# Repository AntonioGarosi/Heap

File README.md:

# Heap
### by Antonio Garosi

Heap is a kid-targeted interactive game aimed at promoting cooperation, fast-thinking and consequentiality.
Ideally, it's a [Tangram](https://en.wikipedia.org/wiki/Tangram) meets [Jenga](https://en.wikipedia.org/wiki/Jenga) meets [Operation](https://en.wikipedia.org/wiki/Operation_(game)) game (this salad is also heavily seasoned with [Beasts of Balance](https://beastsofbalance.com/)'s sauce).

The game was initially conceived to be themed about ecological issues, and the questions are accordingly based on reports about italian waste production.
Expanding the game to other subjects is just a matter of choosing new pairings of questions and answers, coding them and updating the game firmware.

As of October 2018, the most tested version of the game is based of the following rules:

* The players have at their disposal a pool of blocks and tiles.
* Blocks of different materials represents different waste byproducts: natural wood for paper, blue acrylic for plastics, white and red PLA for generic waste. Each block also represents a quantity expressed by its size. Each cube it is made of represents 10kg.
* Each tile is numbered and represents a question.
* The players start a question by placing a card over the central base of the game. Each question is about quantity and they can replied by placing the blocks over the tile.
* If the amount and type of blocks placed over the tile properly answers its question the players can keep building the heap by adding tiles and blocks and so on.
* If the players the players place the wrong amount or type of blocks, the base shakes and the heap crumbles.
* If the players don't reply quick enough, the base shakes and the heap crumbles.
* If the players inadvertently remove or make fall blocks from the heap, the base shakes and ...yep, the heap crumbles.
* If the heap crumbles down, the game is lost.

Full explanation and production details of the project can be found in the [original documentation](http://fab.academany.org/2018/labs/fablabsiena/students/antonio-garosi/final-project/), realized as a final project for my Fab Academy course in 2018.

Everything regarding Heap is under [Creative Commons BY-SA 4.0](https://creativecommons.org/licenses/by-sa/4.0/). Respect this will and everything will be just fine.

For any reason, just [contact me](mailto:antonio_garosi@yahoo.it)

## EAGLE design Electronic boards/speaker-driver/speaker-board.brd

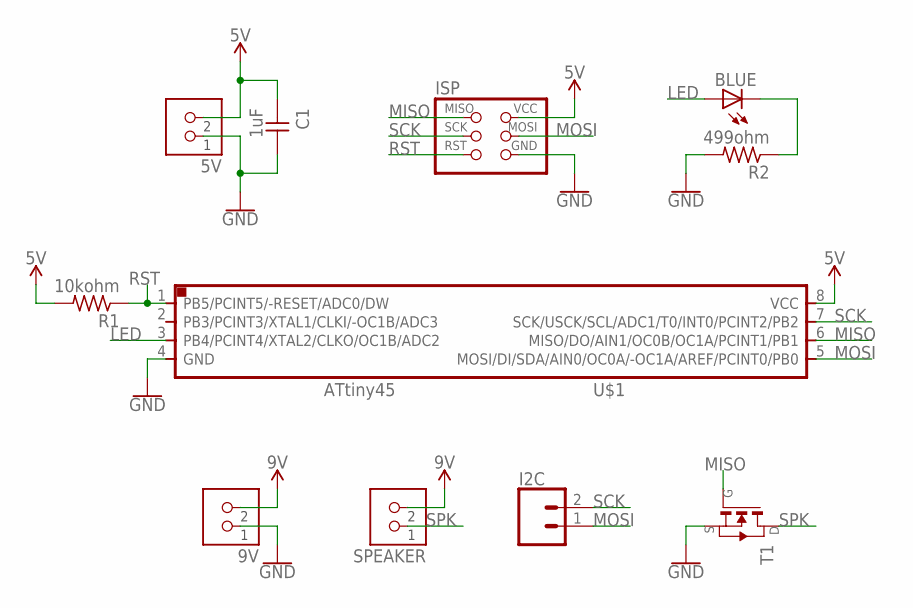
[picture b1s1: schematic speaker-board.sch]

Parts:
5V, 9V: TERM-1X02-FABLAB; ED555DS-2DS
BLUE: LEDFAB1206; LED1206FAB
C1: 1uF; C1206FAB
I2C: CONN_021X02_NO_SILK; 1X02_NO_SILK
ISP: AVRISPSMD; 2X03SMD
R1: 10kohm; R1206FAB
R2: 499ohm; R1206FAB
SPEAKER: TERM-1X02-FABLAB; ED555DS-2DS
T1: NMOSFETSOT23; SOT-23
U$1: ATTINY45SI; SOIC8

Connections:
GND: 5V.1, 9V.1, C1.2, ISP.6 (GND), R2.2, T1.2 (S), U$1.4 (GND)
LED: BLUE.1 (A), U$1.3 (PB4/PCINT4/XTAL2/CLKO/OC1B/ADC2)
MISO: ISP.1 (MISO), T1.3 (G), U$1.6 (MISO/DO/AIN1/OC0B/OC1A/PCINT1/PB1)
MOSI: I2C.1, ISP.4 (MOSI), U$1.5 (MOSI/DI/SDA/AIN0/OC0A/-OC1A/AREF/PCINT0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)
unnamed: BLUE.2 (C), R2.1
RST: ISP.5 (RST), R1.1, U$1.1 (PB5/PCINT5/-RESET/ADC0/DW)
SCK: I2C.2, ISP.3 (SCK), U$1.7 (SCK/USCK/SCL/ADC1/T0/INT0/PCINT2/PB2)
SPK: SPEAKER.1, T1.1 (D)
VCC_1: 5V.2, C1.1, ISP.2 (VCC), R1.2, U$1.8 (VCC)
VCC_2: 9V.2, SPEAKER.2

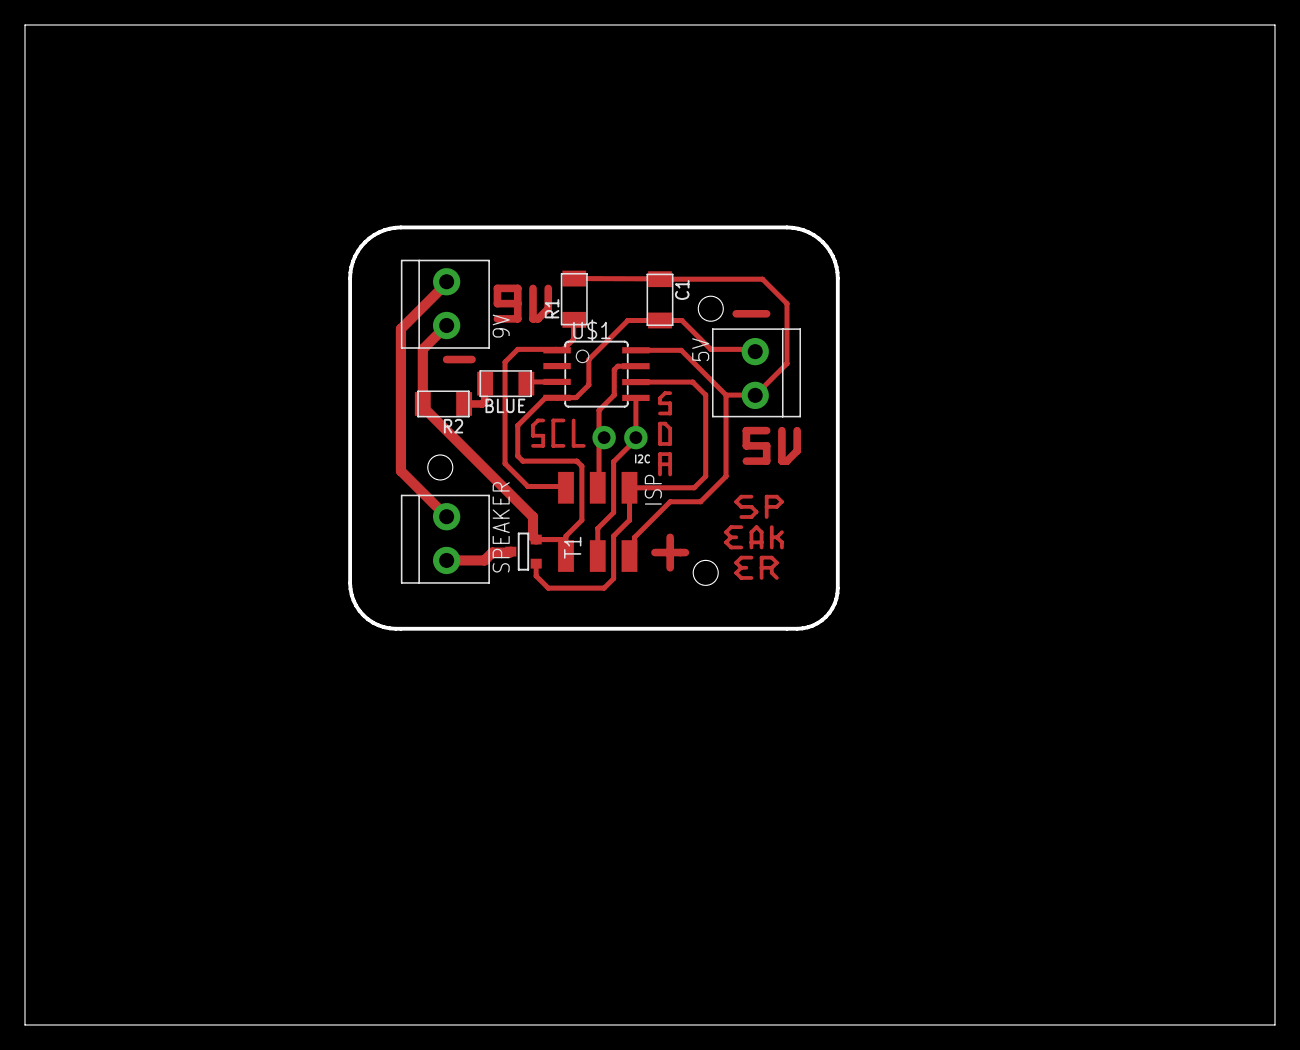
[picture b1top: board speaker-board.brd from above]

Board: 2 copper layers, 100.0 x 80.0 mm, 11 parts (0 on the bottom side), 10 nets.

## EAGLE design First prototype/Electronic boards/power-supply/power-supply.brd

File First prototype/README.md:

# Heap
### by Antonio Garosi - July 2018

**This files hold the design of the very first, complete, functional prototype made as final project for my Fab Academy 2018 course.
The root of this repository will be continuosly updated but this folder will always remain as is to remark the starting point of this project.**

Heap is a kid-targeted interactive game about waste production, aimed at promoting cooperation, fast-thinking and consequentiality.
Ideally, it's a game where [Tangram](https://en.wikipedia.org/wiki/Tangram) meets [Jenga](https://en.wikipedia.org/wiki/Jenga) meets [Operation](https://en.wikipedia.org/wiki/Operation_(game)).
The rules are by design loose and open, but essentially they are as such:

* The players are presented with a pool filled with a set of cards representing daily items and various blocks of different colors and shapes;

* Within a time span, the players have to choose among one of the cards and put it on the base at the center of the pool;

* Then, within another and shorter time span, the players will have to put over the card a precise amount of blocks, trying to recreate the figure over the card. The material of the block represents a different kind of waste, so, in addition to the shape, the players will have to guess the material of which the item over the card is made of;

* A load sensor under the base evaluates the blocks over the card. The more the load is far from the corresponding value, the more more the base will begin to nervously buzz and shake;

* If the stack is still in place new cards and blocks can be added. If the stack tumbles down the game will start all over again;

Full explanation and production details of the project can be found in the [original documentation](http://fab.academany.org/2018/labs/fablabsiena/students/antonio-garosi/final-project/), realized as a final project for my Fab Academy course in 2018.

Everything regarding Heap is under [Creative Commons BY-SA 4.0](https://creativecommons.org/licenses/by-sa/4.0/). Respect this will and everything will be just fine.

For any reason, just [contact me](mailto:antonio_garosi@yahoo.it).

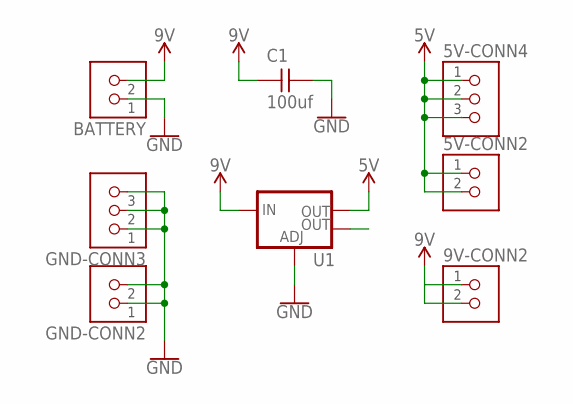
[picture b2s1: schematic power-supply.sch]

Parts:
5V-CONN2, 9V-CONN2: TERM-1X02-FABLAB; ED555DS-2DS
5V-CONN4: TERM-1X03'-FABLAB'; ED555DS-3DS
BATTERY: TERM-1X02-FABLAB; ED555DS-2DS
C1: 100uf; C1206FAB
GND-CONN2: TERM-1X02-FABLAB; ED555DS-2DS
GND-CONN3: TERM-1X03'-FABLAB'; ED555DS-3DS
U1: V_REG_LM1117SOT223; SOT223

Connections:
5V: 5V-CONN2.1, 5V-CONN2.2, 5V-CONN4.1, 5V-CONN4.2, 5V-CONN4.3, U1.2 (OUT)
9V: 9V-CONN2.1, 9V-CONN2.2, BATTERY.2, C1.1, U1.3 (IN)
GND: BATTERY.1, C1.2, GND-CONN2.1, GND-CONN2.2, GND-CONN3.1, GND-CONN3.2, GND-CONN3.3, U1.1 (ADJ)

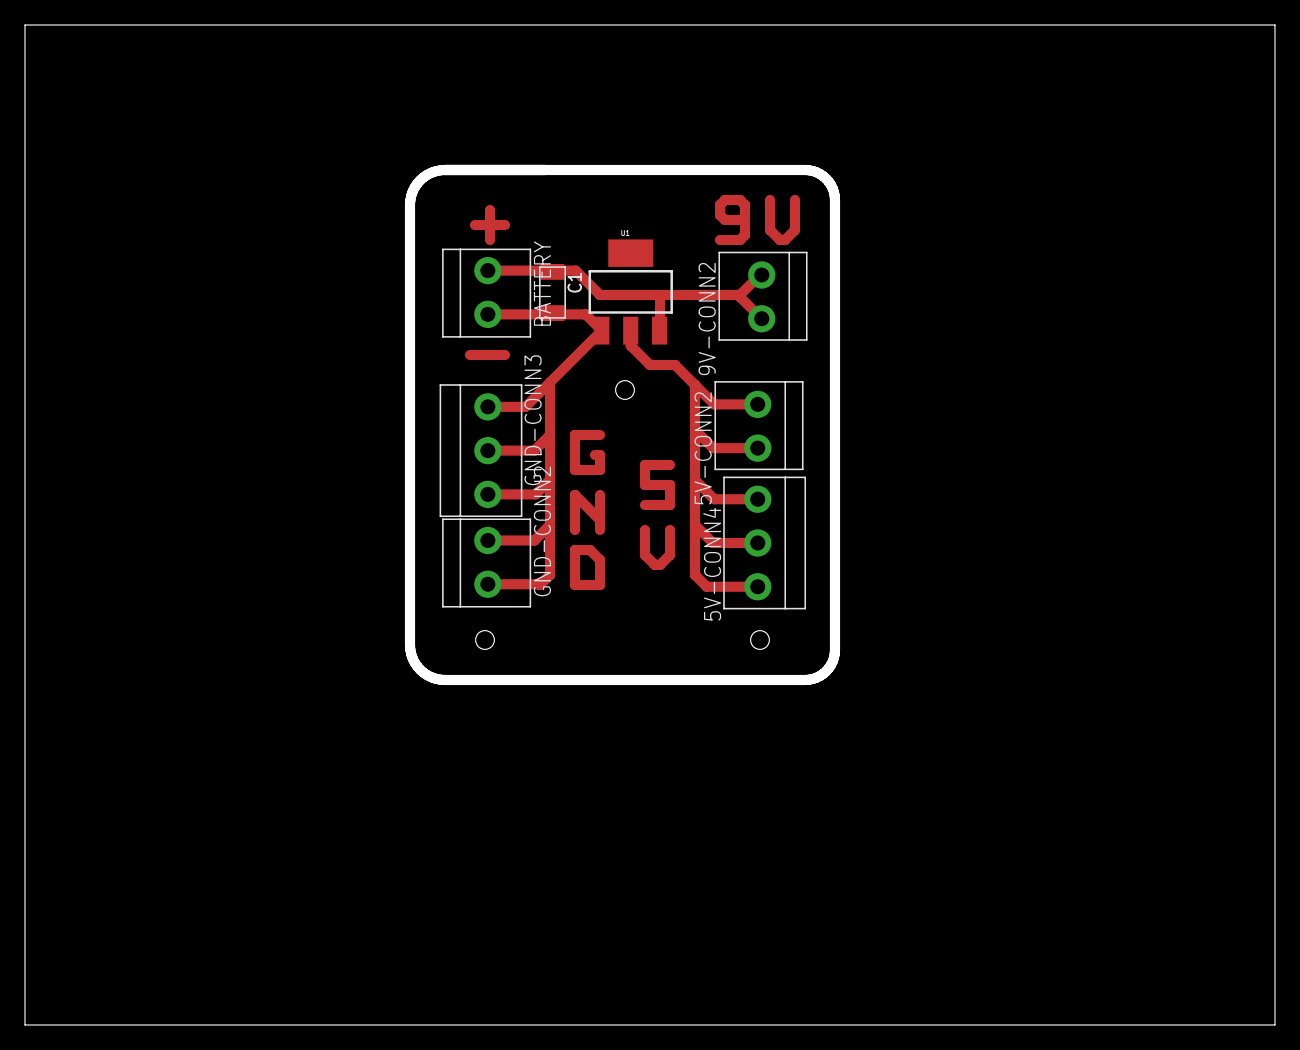
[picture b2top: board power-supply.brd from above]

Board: 2 copper layers, 100.0 x 80.0 mm, 8 parts (0 on the bottom side), 3 nets.

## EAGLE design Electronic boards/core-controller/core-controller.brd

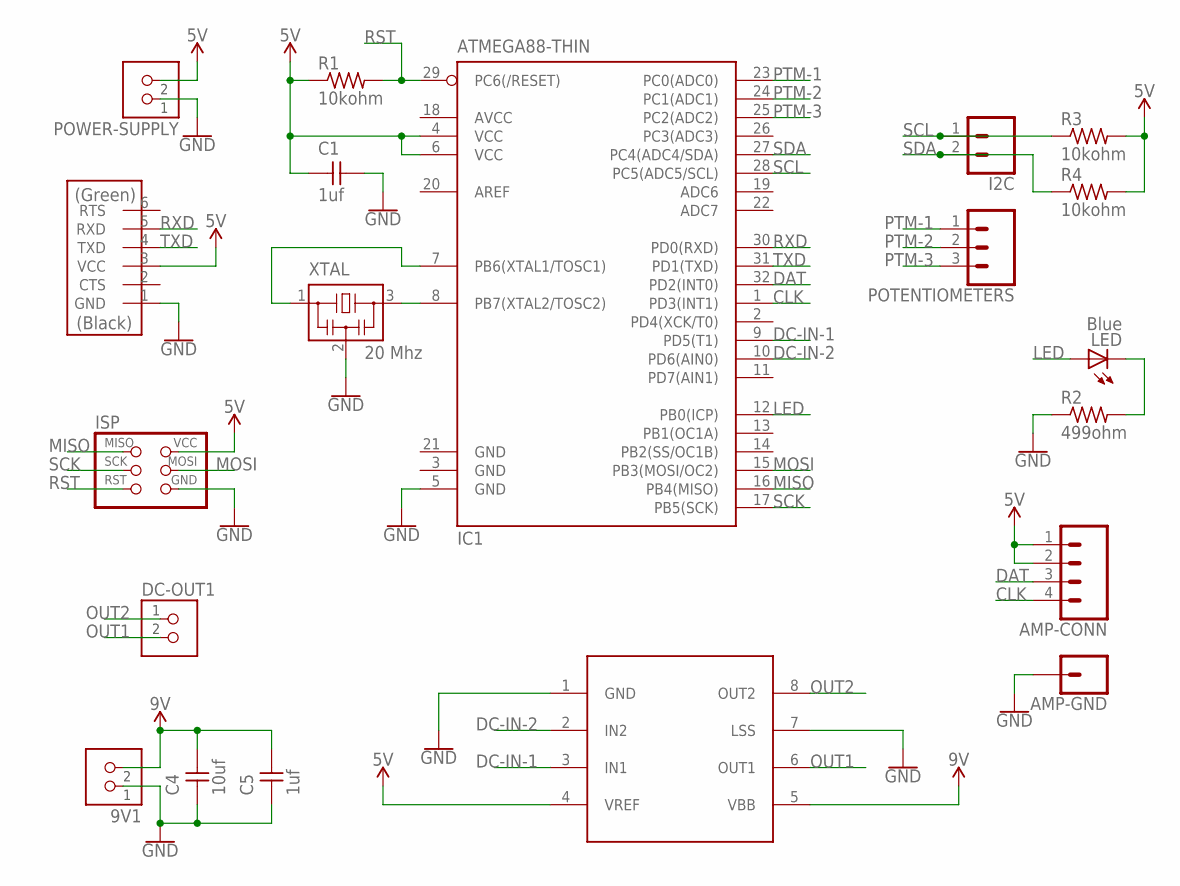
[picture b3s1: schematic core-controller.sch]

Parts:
9V1: TERM-1X02-FABLAB; ED555DS-2DS
AMP-CONN: CONN_041X04_NO_SILK; 1X04_NO_SILK
AMP-GND: CONN_01PTH_NO_SILK_YES_STOP; 1X01_NO_SILK
C1, C5: 1uf; C1206FAB
C4: 10uf; C1206FAB
DC-OUT1: TERM-1X02-FABLAB; ED555DS-2DS
FTDI: FTDI; 1X06SMD
I2C: CONN_021X02_NO_SILK; 1X02_NO_SILK
IC1: ATMEGA88-THIN; TQFP32-08THIN
ISP: AVRISPSMD; 2X03SMD
LED: Blue; LED1206FAB
POTENTIOMETERS: CONN_031X03_NO_SILK; 1X03_NO_SILK
POWER-SUPPLY: TERM-1X02-FABLAB; ED555DS-2DS
R1, R3, R4: 10kohm; R1206FAB
R2: 499ohm; R1206FAB
U$2: A4953; SOIC8
XTAL: 20 Mhz; EFOBM

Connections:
5V: AMP-CONN.1, AMP-CONN.2, C1.1, FTDI.3 (VCC), IC1.4 (VCC), IC1.6 (VCC), ISP.2 (VCC), POWER-SUPPLY.2, R1.1, R3.2, R4.2, U$2.4 (VREF)
AVCC: IC1.18 (AVCC)
CLK: AMP-CONN.4, IC1.1 (PD3(INT1))
DAT: AMP-CONN.3, IC1.32 (PD2(INT0))
DC-IN-1: IC1.9 (PD5(T1)), U$2.3 (IN1)
DC-IN-2: IC1.10 (PD6(AIN0)), U$2.2 (IN2)
GND: 9V1.1, AMP-GND.1, C1.2, C4.1, C5.1, FTDI.1 (GND), IC1.3 (GND), IC1.5 (GND), IC1.21 (GND), ISP.6 (GND), POWER-SUPPLY.1, R2.1, U$2.1 (GND), U$2.7 (LSS), XTAL.2
LED: IC1.12 (PB0(ICP)), LED.1 (A)
MISO: IC1.16 (PB4(MISO)), ISP.1 (MISO)
MOSI: IC1.15 (PB3(MOSI/OC2)), ISP.4 (MOSI)
unnamed: IC1.7 (PB6(XTAL1/TOSC1)), XTAL.1
unnamed: IC1.8 (PB7(XTAL2/TOSC2)), XTAL.3
unnamed: LED.2 (C), R2.2
OUT1: DC-OUT1.2, U$2.6 (OUT1)
OUT2: DC-OUT1.1, U$2.8 (OUT2)
PTM-1: IC1.23 (PC0(ADC0)), POTENTIOMETERS.1
PTM-2: IC1.24 (PC1(ADC1)), POTENTIOMETERS.2
PTM-3: IC1.25 (PC2(ADC2)), POTENTIOMETERS.3
RST: IC1.29 (PC6(/RESET)), ISP.5 (RST), R1.2
RXD: FTDI.5 (RXD), IC1.30 (PD0(RXD))
SCK: IC1.17 (PB5(SCK)), ISP.3 (SCK)
SCL: I2C.1, IC1.28 (PC5(ADC5/SCL)), R3.1
SDA: I2C.2, IC1.27 (PC4(ADC4/SDA)), R4.1
TXD: FTDI.4 (TXD), IC1.31 (PD1(TXD))
VDD: 9V1.2, C4.2, C5.2, U$2.5 (VBB)

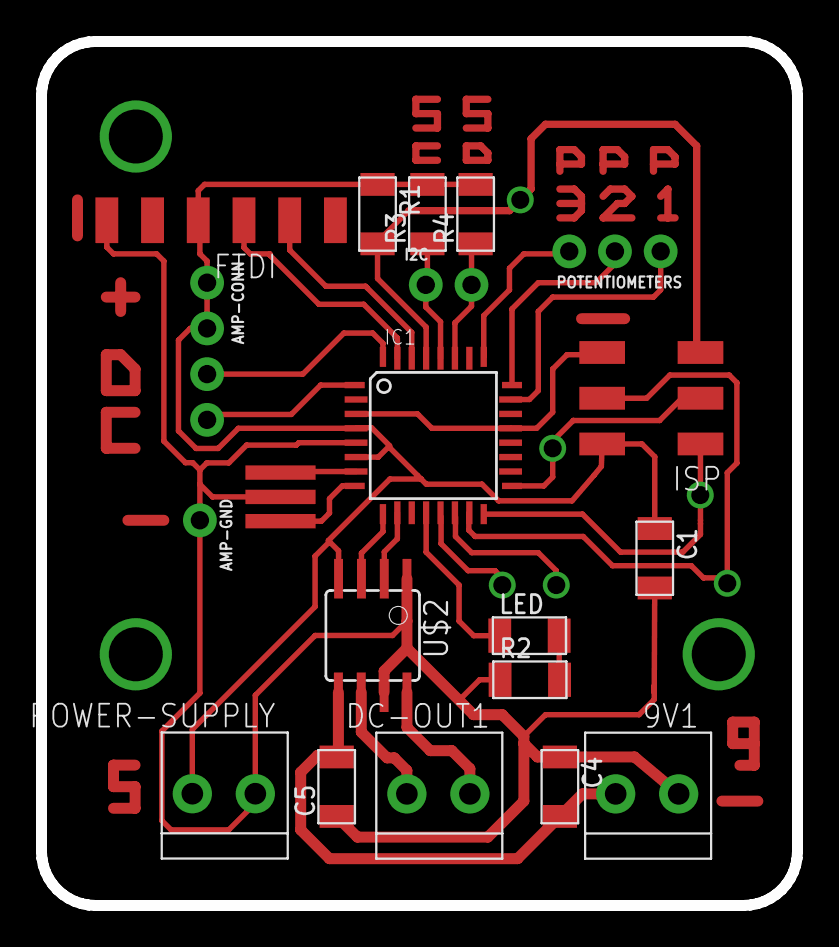
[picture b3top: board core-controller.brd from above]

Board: 2 copper layers, 42.0 x 48.0 mm, 20 parts (0 on the bottom side), 24 nets.

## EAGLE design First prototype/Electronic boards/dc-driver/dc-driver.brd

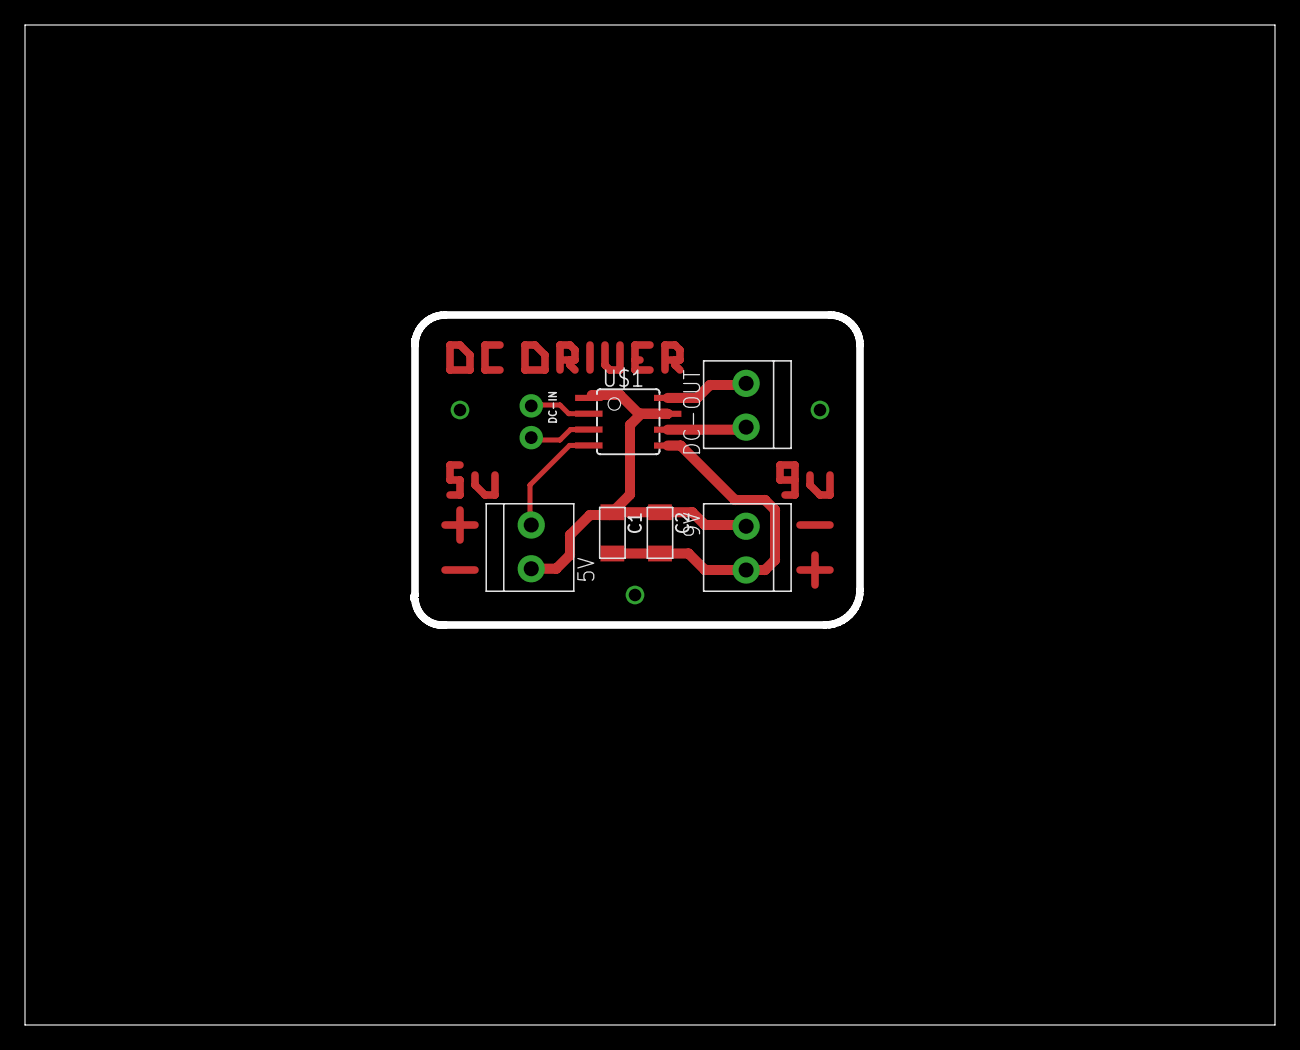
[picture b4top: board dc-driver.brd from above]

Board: 2 copper layers, 100.0 x 80.0 mm, 7 parts (0 on the bottom side), 7 nets.

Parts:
5V, 9V: TERM-1X02-FABLAB; ED555DS-2DS
C1: 10uf; C1206FAB
C2: 1uf; C1206FAB
DC-IN: 1X02_NO_SILK
DC-OUT: TERM-1X02-FABLAB; ED555DS-2DS
U$1: A4953; SOIC8

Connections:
DC-IN-1: DC-IN.2, U$1.3
DC-IN-2: DC-IN.1, U$1.2
GND: 5V.1, 9V.1, C1.1, C2.1, U$1.1, U$1.7
OUT1: DC-OUT.2, U$1.6
OUT2: DC-OUT.1, U$1.8
VCC: 5V.2, U$1.4
VDD: 9V.2, C1.2, C2.2, U$1.5

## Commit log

2018-04-12 another try
2018-04-12 Delete
2018-04-13 Update presentation and logo
2018-06-07 added electronics
2018-06-07 Added boards
2018-06-11 Update various things
2018-06-13 Updated graphic material
2018-06-13 Various updates
2018-06-14 Product design updates
2018-07-04 Many changes
2018-07-04 Simple update, nothing serious
2018-07-04 Update logos and links
2018-07-04 Fix on a markdown typo
2018-07-28 New pc!
2018-07-28 Created folder for First Prototype and updated Core Controller board (with dc driver in itself, hence dc driver board is no more)
2018-10-15 Updated sevaral things: blocks and structure designs, electronic boards, usability of the product, etc.
2018-10-15 Left behind from previous push
2018-10-16 Added board base files. Fixed few file names
2018-10-16 Graphic design updates
2018-10-18 Updated wood decoration
2018-11-04 Updated Presentation Material, added Documentation folder, updated core board code

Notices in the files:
parts and their libraries:
SparkFun-Connectors: Licensing: Creative Commons ShareAlike 4.0 International - https://creativecommons.org/licenses/by-sa/4.0
